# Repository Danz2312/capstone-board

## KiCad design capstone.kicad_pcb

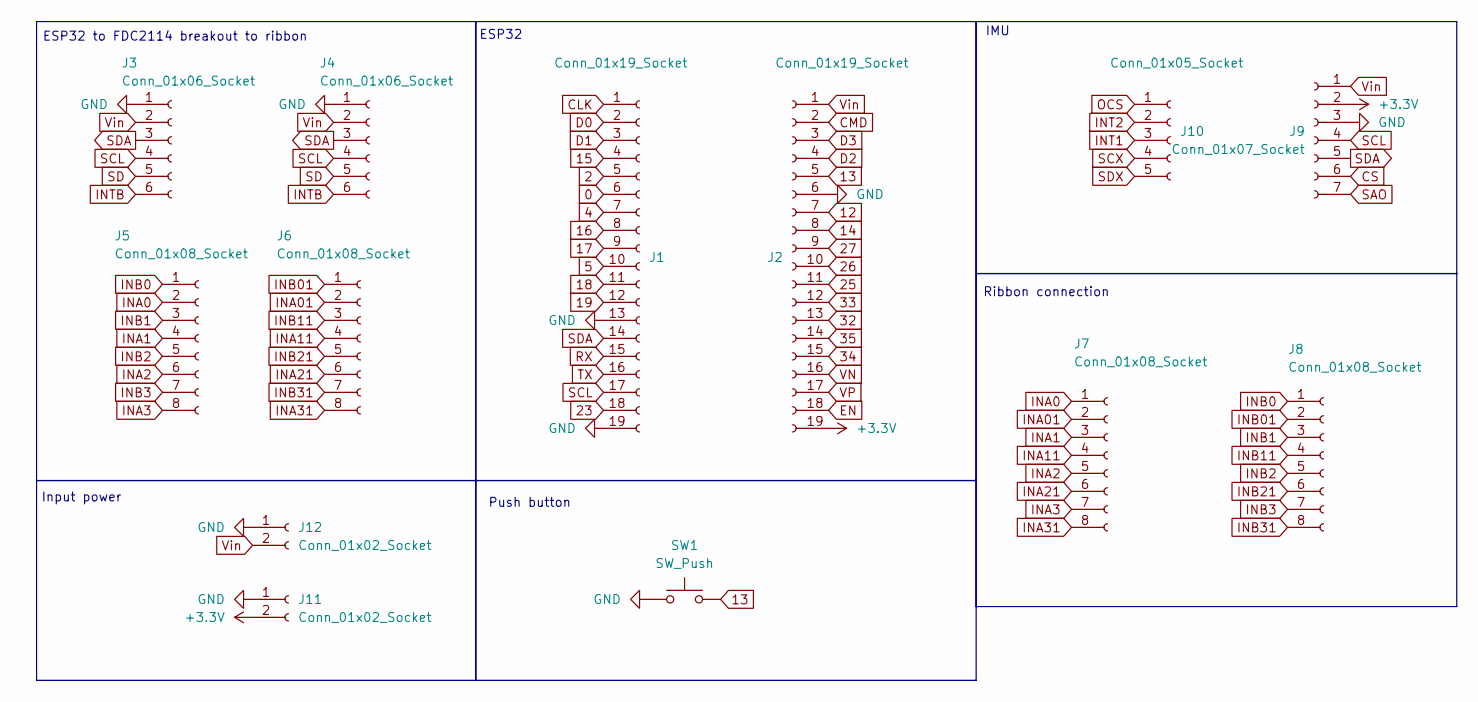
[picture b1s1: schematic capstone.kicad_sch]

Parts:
J1, J2: Conn_01x19_Socket; PinHeader_1x19_P2.54mm_Vertical
J3, J4: Conn_01x06_Socket; PinHeader_1x06_P2.54mm_Vertical
J5, J6: Conn_01x08_Socket; PinHeader_1x08_P2.54mm_Vertical
J7, J8: Conn_01x08_Socket; TE_84952-8_1x08-1MP_P1.0mm_Horizontal
J9: Conn_01x07_Socket; PinHeader_1x07_P2.54mm_Vertical
J10: Conn_01x05_Socket; PinHeader_1x05_P2.54mm_Vertical
J11, J12: Conn_01x02_Socket; PinHeader_1x02_P2.54mm_Vertical
SW1: SW_Push; SW_PUSH_6mm

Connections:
0: J1.6
2: J1.5
4: J1.7
5: J1.10
12: J2.7
13: J2.5, SW1.2
14: J2.8
15: J1.4
16: J1.8
17: J1.9
18: J1.11
19: J1.12
23: J1.18
25: J2.11
26: J2.10
27: J2.9
32: J2.13
33: J2.12
34: J2.15
35: J2.14
+3.3V: J2.19, J9.2, J11.2
CLK: J1.1
CMD: J2.2
CS: J9.6
D0: J1.2
D1: J1.3
D2: J2.4
D3: J2.3
EN: J2.18
GND: J1.13, J1.19, J2.6, J3.1, J4.1, J9.3, J11.1, J12.1, SW1.1
INA0: J5.2, J7.1
INA1: J5.4, J7.3
INA01: J6.2, J7.2
INA2: J5.6, J7.5
INA3: J5.8, J7.7
INA11: J6.4, J7.4
INA21: J6.6, J7.6
INA31: J6.8, J7.8
INB0: J5.1, J8.1
INB1: J5.3, J8.3
INB01: J6.1, J8.2
INB2: J5.5, J8.5
INB3: J5.7, J8.7
INB11: J6.3, J8.4
INB21: J6.5, J8.6
INB31: J6.7, J8.8
INT1: J10.3
INT2: J10.2
INTB: J3.6, J4.6
OCS: J10.1
RX: J1.15
SAO: J9.7
SCL: J1.17, J3.4, J4.4, J9.4
SCX: J10.4
SD: J3.5, J4.5
SDA: J1.14, J3.3, J4.3, J9.5
SDX: J10.5
TX: J1.16
VN: J2.16
VP: J2.17
Vin: J2.1, J3.2, J4.2, J9.1, J12.2

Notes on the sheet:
Input power
ESP32
IMU
Push button
Ribbon connection
ESP32 to FDC2114 breakout to ribbon

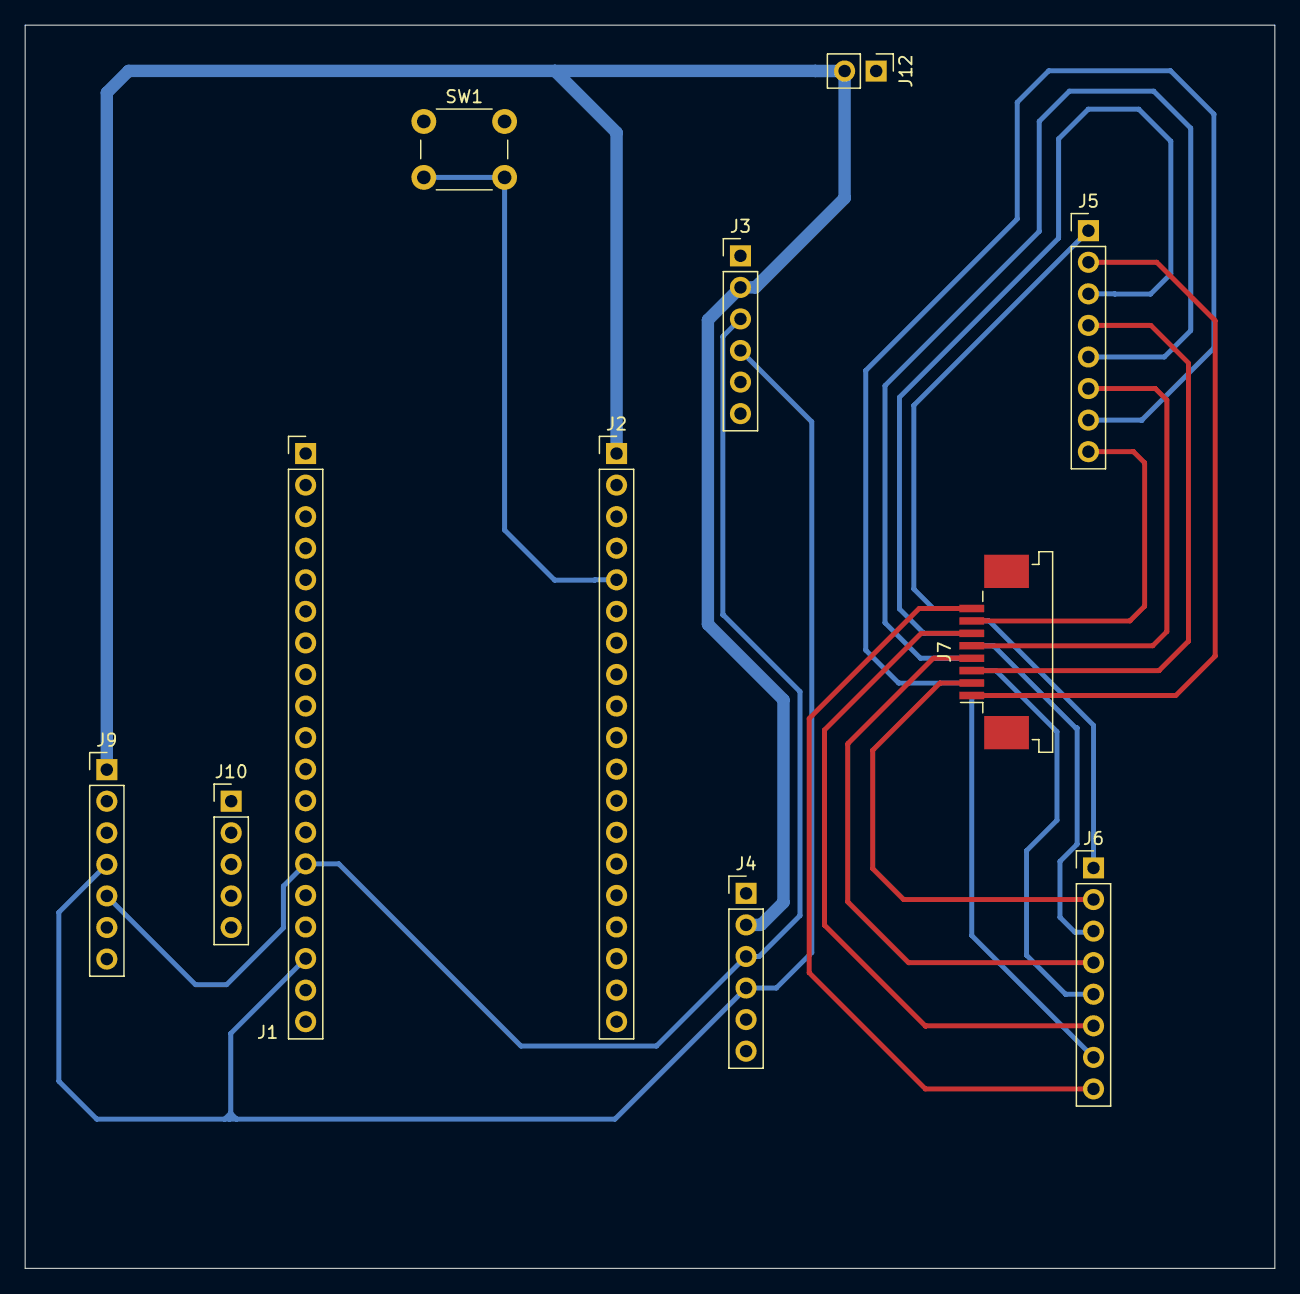
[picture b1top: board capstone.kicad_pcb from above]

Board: 2 copper layers, 100.6 x 100.0 mm, 12 parts (1 on the bottom side), 24 nets.

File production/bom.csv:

Designator,Footprint,Quantity,Value,LCSC Part #
"J1, J2",PinHeader_1x19_P2.54mm_Vertical,2,Conn_01x19_Socket,
J10,PinHeader_1x05_P2.54mm_Vertical,1,Conn_01x05_Socket,
J12,PinHeader_1x02_P2.54mm_Vertical,1,Conn_01x02_Socket,
"J3, J4",PinHeader_1x06_P2.54mm_Vertical,2,Conn_01x06_Socket,
"J5, J6",PinHeader_1x08_P2.54mm_Vertical,2,Conn_01x08_Socket,
"J7, J8",TE_84952-8_1x08-1MP_P1.0mm_Horizontal,2,Conn_01x08_Socket,
J9,PinHeader_1x07_P2.54mm_Vertical,1,Conn_01x07_Socket,
SW1,SW_PUSH_6mm,1,SW_Push,
